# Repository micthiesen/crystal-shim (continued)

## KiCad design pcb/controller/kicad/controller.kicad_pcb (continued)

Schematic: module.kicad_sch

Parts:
C5: 22uF; Controller_C5; MPN GRM32ER71E226ME15L
C6: 100nF; Controller_C6; MPN C1608X7R1H104K080AA
C9: 1uF; Controller_C9; MPN C2012X7R1E105K125AB
D4: WP710A10LGD; Controller_D4; MPN WP710A10LGD
R50: 10kΩ; Controller_R50; MPN ERJ3EKF1002V
R51: 10kΩ; Controller_R51; MPN ERJ3EKF1002V
R52: 10kΩ; Controller_R52; MPN ERJ3EKF1002V
R53: 10kΩ; Controller_R53; MPN ERJ3EKF1002V
R54: 680Ω; Controller_R54; MPN ERJ3EKF6800V
R55: 330Ω; Controller_R55; MPN ERJ3EKF3300V
SW1: B3F-1002-G; Controller_SW1; MPN B3F-1002-G
SW2: B3F-1002-G; Controller_SW2; MPN B3F-1002-G
SW3: B3F-1002-G; Controller_SW3; MPN B3F-1002-G
U1: ESP32-C6-WROOM-1-N8; Controller_U1; MPN ESP32-C6-WROOM-1-N8

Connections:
ACCESSORY_INPUT1: U1.4 (IO4); also elsewhere on the board
ACCESSORY_INPUT2: U1.5 (IO5); also elsewhere on the board
BOOT_N: R51.2, SW2.1 (CONTACT_A), U1.15 (IO9)
BOOT_STRAP8: R52.2, U1.10 (IO8)
CHIP_EN: C9.1, R53.2, R55.1, U1.3 (EN); also elsewhere on the board
GND: C5.2, C6.2, C9.2, D4.1 (K), SW1.2 (CONTACT_B), SW2.2 (CONTACT_B), SW3.2 (CONTACT_B), U1.1 (GND_1), U1.28 (GND_28), U1.29 (GND_EP); also elsewhere on the board
LED_ANODE: D4.2 (A), R54.2
MAINTENANCE_N: R50.2, SW1.1 (CONTACT_A), U1.12 (IO11)
PSU_GOOD: U1.19 (IO21); also elsewhere on the board
PUMP_CHLORINE: U1.27 (IO2); also elsewhere on the board
PUMP_DECHLOR: U1.26 (IO3); also elsewhere on the board
PUMP_TRANSFER: U1.9 (IO1); also elsewhere on the board
RELAY_REQUEST: U1.11 (IO10); also elsewhere on the board
RESERVOIR_SCL: U1.7 (IO7); also elsewhere on the board
RESERVOIR_SDA: U1.6 (IO6); also elsewhere on the board
RESET_CONTACT: R55.2, SW3.1 (CONTACT_A)
SENSOR_BUS_EN: U1.8 (IO0); also elsewhere on the board
SENSOR_POWER_EN: U1.20 (IO22); also elsewhere on the board
SENSOR_POWER_FAULT_N: U1.21 (IO23); also elsewhere on the board
SENSOR_SCL: U1.17 (IO19); also elsewhere on the board
SENSOR_SDA: U1.16 (IO18); also elsewhere on the board
STATUS_LED: R54.1, U1.18 (IO20)
UART0_RX: U1.24 (RXD0_IO17); also elsewhere on the board
UART0_TX: U1.25 (TXD0_IO16); also elsewhere on the board
USB_D_N: U1.13 (IO12); also elsewhere on the board
USB_D_P: U1.14 (IO13); also elsewhere on the board
V3V3: C5.1, C6.1, R50.1, R51.1, R52.1, R53.1, U1.2 (V3V3); also elsewhere on the board

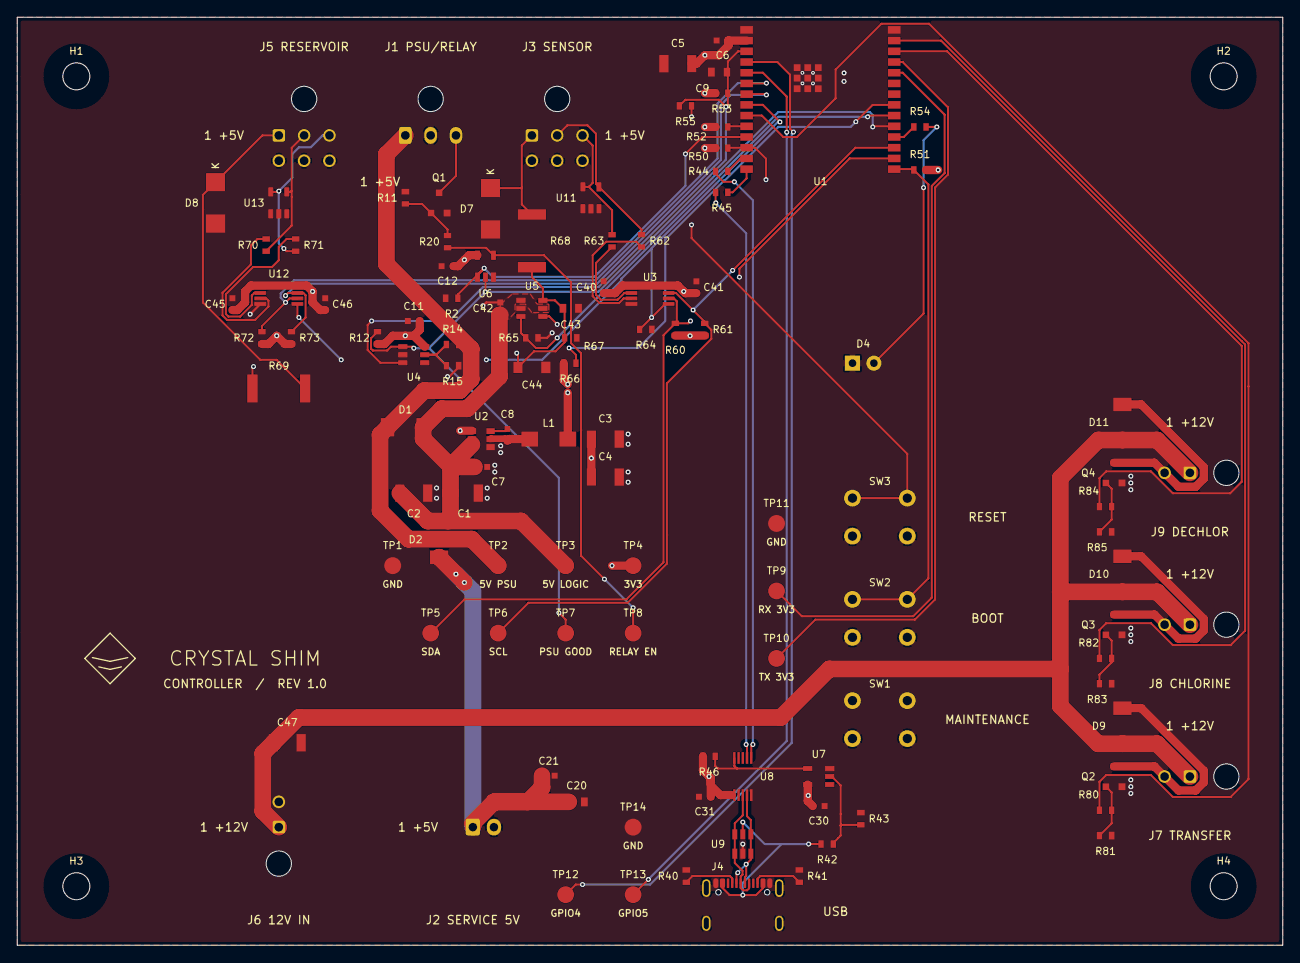
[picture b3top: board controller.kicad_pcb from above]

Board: 4 copper layers, 150.0 x 110.0 mm, 117 parts (0 on the bottom side), 63 nets.

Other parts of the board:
H1: 3.2mm NPTH; Controller_H1
H2: 3.2mm NPTH; Controller_H2
H3: 3.2mm NPTH; Controller_H3
H4: 3.2mm NPTH; Controller_H4
